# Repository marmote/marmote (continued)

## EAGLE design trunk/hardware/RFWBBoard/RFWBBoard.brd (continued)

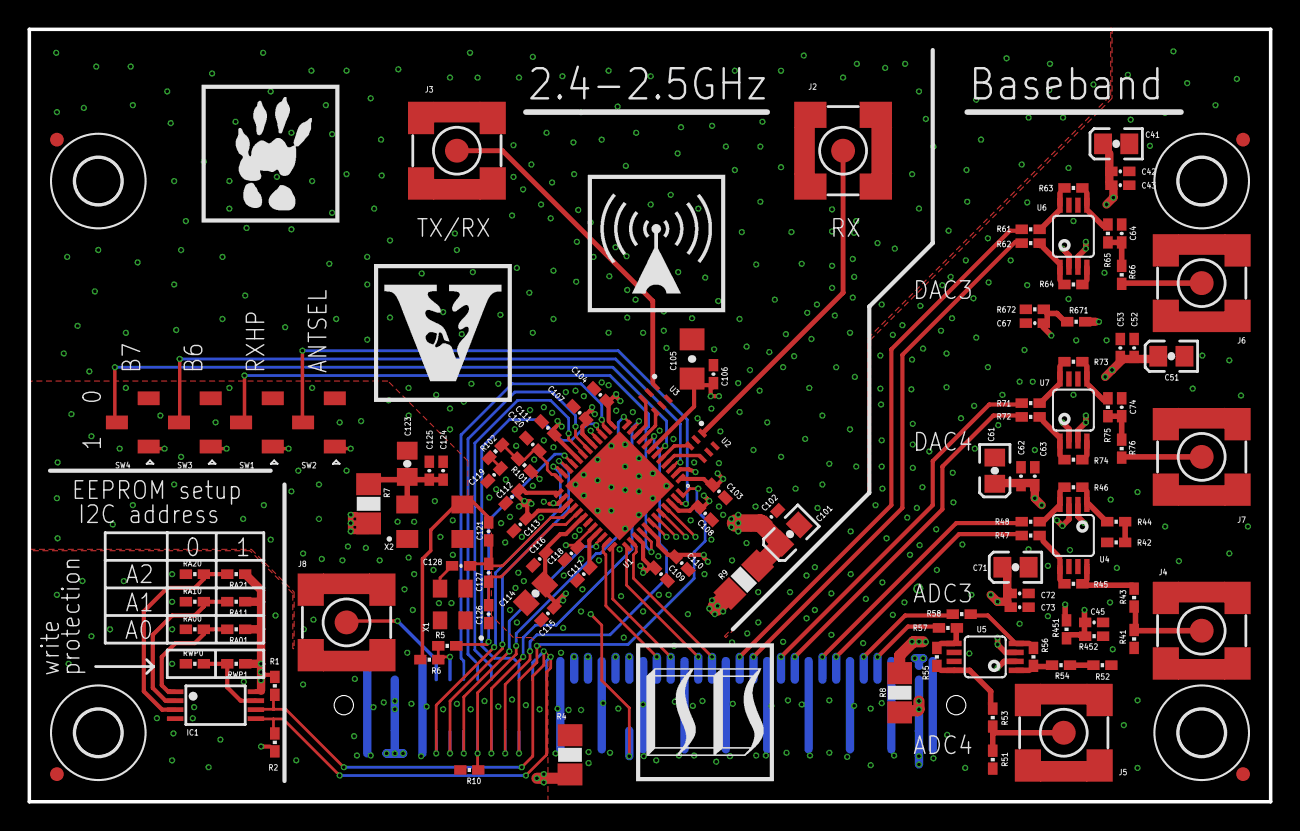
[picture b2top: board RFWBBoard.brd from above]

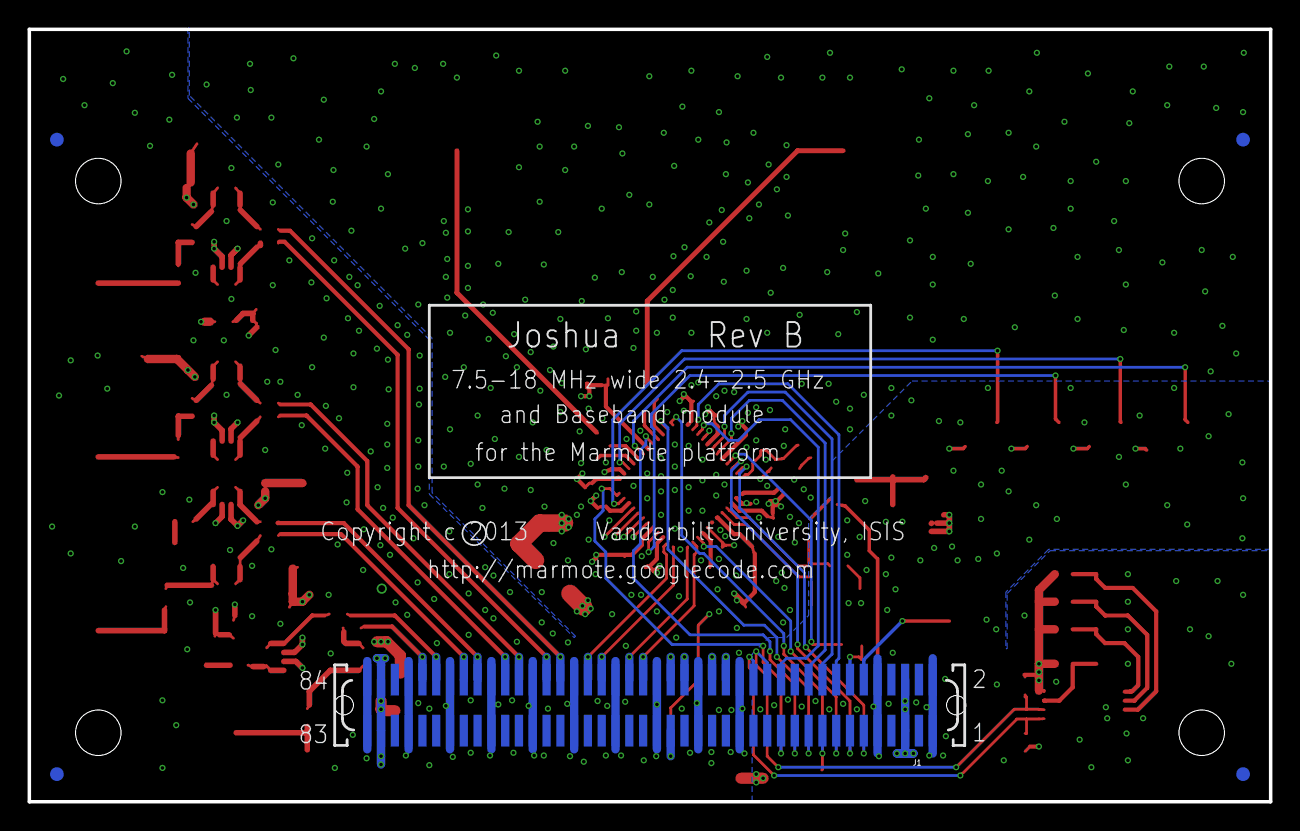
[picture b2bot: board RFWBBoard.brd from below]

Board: 6 copper layers, 90.0 x 56.0 mm, 132 parts (5 on the bottom side), 91 nets.

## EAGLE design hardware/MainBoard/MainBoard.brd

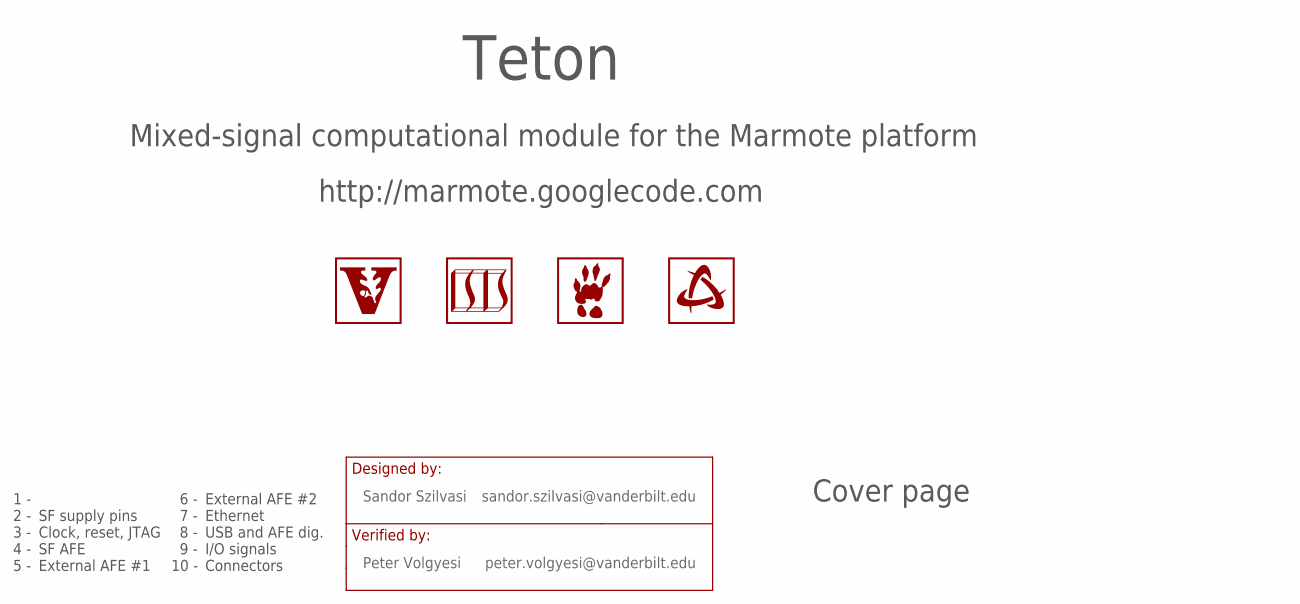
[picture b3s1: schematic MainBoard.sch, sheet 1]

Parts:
LOGO1: LOGO-VANDERBILT-600MIL-10MM-SS; LOGO-VANDERBILT-10MM-SILKSCREEN
LOGO2: LOGO-ISIS-600MIL-10MM-SS; LOGO-ISIS-10MM-SILKSCREEN
LOGO3: LOGO-MARMOTE-600MIL-10MM-SS; LOGO-MARMOTE-10MM-SILKSCREEN
LOGO4: LOGO-SMARTFUSION-600MIL-10MM-SS; LOGO-SMARTFUSION-10MM-SILKSCREEN

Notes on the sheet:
Mixed-signal computational module for the Marmote platform
http://marmote.googlecode.com
1 -
2 -
3 -
4 -
5 -
6 -
7 -
8 -
9 -
10 -

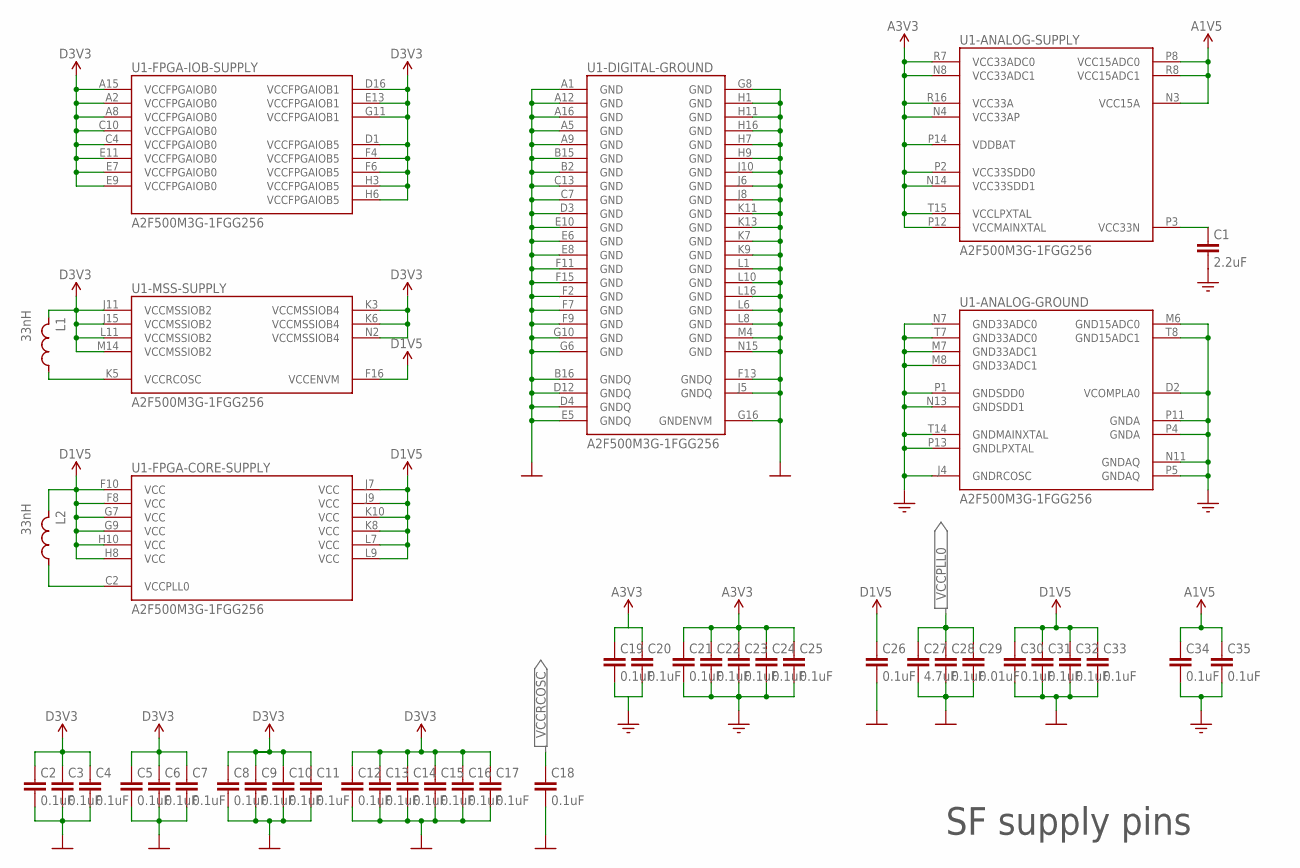
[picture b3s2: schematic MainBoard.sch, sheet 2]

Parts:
C1: 2.2uF; C0402
C2, C3, C4, C5, C6, C7, C8, C9, C10, C11, C12, C13, C14, C15, C16, C17, C18, C19, C20, C21, C22, C23, C24, C25, C26, C28, C30, C31, C32, C33, C34, C35: 0.1uF; C0402
C27: 4.7uF; C0402
C29: 0.01uF; C0402
L1, L2: 33nH; L0603
U1: A2F500M3G-1FGG256; FG256

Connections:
A1V5: C34.1, C35.1, U1.N3 (VCC15A), U1.P8 (VCC15ADC0), U1.R8 (VCC15ADC1); also elsewhere on the board
A3V3: C19.1, C20.1, C21.1, C22.1, C23.1, C24.1, C25.1, U1.N4 (VCC33AP), U1.N8 (VCC33ADC1), U1.N14 (VCC33SDD1), U1.P2 (VCC33SDD0), U1.P12 (VCCMAINXTAL), U1.P14 (VDDBAT), U1.R7 (VCC33ADC0), U1.R16 (VCC33A), U1.T15 (VCCLPXTAL); also elsewhere on the board
AGND: C1.2, C19.2, C20.2, C21.2, C22.2, C23.2, C24.2, C25.2, C34.2, C35.2, U1.D2 (VCOMPLA0), U1.J4 (GNDRCOSC), U1.M6 (GND15ADC0), U1.M7 (GND33ADC1), U1.M8 (GND33ADC1), U1.N7 (GND33ADC0), U1.N11 (GNDAQ), U1.N13 (GNDSDD1), U1.P1 (GNDSDD0), U1.P4 (GNDA), U1.P5 (GNDAQ), U1.P11 (GNDA), U1.P13 (GNDLPXTAL), U1.T7 (GND33ADC0), U1.T8 (GND15ADC1), U1.T14 (GNDMAINXTAL); also elsewhere on the board
D1V5: C26.1, C30.1, C31.1, C32.1, C33.1, L2.2, U1.F8 (VCC), U1.F10 (VCC), U1.F16 (VCCENVM), U1.G7 (VCC), U1.G9 (VCC), U1.H8 (VCC), U1.H10 (VCC), U1.J7 (VCC), U1.J9 (VCC), U1.K8 (VCC), U1.K10 (VCC), U1.L7 (VCC), U1.L9 (VCC); also elsewhere on the board
D3V3: C2.1, C3.1, C4.1, C5.1, C6.1, C7.1, C8.1, C9.1, C10.1, C11.1, C12.1, C13.1, C14.1, C15.1, C16.1, C17.1, L1.2, U1.A2 (VCCFPGAIOB0), U1.A8 (VCCFPGAIOB0), U1.A15 (VCCFPGAIOB0), U1.C4 (VCCFPGAIOB0), U1.C10 (VCCFPGAIOB0), U1.D1 (VCCFPGAIOB5), U1.D16 (VCCFPGAIOB1), U1.E7 (VCCFPGAIOB0), U1.E9 (VCCFPGAIOB0), U1.E11 (VCCFPGAIOB0), U1.E13 (VCCFPGAIOB1), U1.F4 (VCCFPGAIOB5), U1.F6 (VCCFPGAIOB5), U1.G11 (VCCFPGAIOB1), U1.H3 (VCCFPGAIOB5), U1.H6 (VCCFPGAIOB5), U1.J11 (VCCMSSIOB2), U1.J15 (VCCMSSIOB2), U1.K3 (VCCMSSIOB4), U1.K6 (VCCMSSIOB4), U1.L11 (VCCMSSIOB2), U1.M14 (VCCMSSIOB2), U1.N2 (VCCMSSIOB4); also elsewhere on the board
DGND: C2.2, C3.2, C4.2, C5.2, C6.2, C7.2, C8.2, C9.2, C10.2, C11.2, C12.2, C13.2, C14.2, C15.2, C16.2, C17.2, C18.2, C26.2, C27.2, C28.2, C29.2, C30.2, C31.2, C32.2, C33.2, U1.A1 (GND), U1.A5 (GND), U1.A9 (GND), U1.A12 (GND), U1.A16 (GND), U1.B2 (GND), U1.B15 (GND), U1.B16 (GNDQ), U1.C7 (GND), U1.C13 (GND), U1.D3 (GND), U1.D4 (GNDQ), U1.D12 (GNDQ), U1.E5 (GNDQ), U1.E6 (GND), U1.E8 (GND), U1.E10 (GND), U1.F2 (GND), U1.F7 (GND), U1.F9 (GND), U1.F11 (GND), U1.F13 (GNDQ), U1.F15 (GND), U1.G6 (GND), U1.G8 (GND), U1.G10 (GND), U1.G16 (GNDENVM), U1.H1 (GND), U1.H7 (GND), U1.H9 (GND), U1.H11 (GND), U1.H16 (GND), U1.J5 (GNDQ), U1.J6 (GND), U1.J8 (GND), U1.J10 (GND), U1.K7 (GND), U1.K9 (GND), U1.K11 (GND), U1.K13 (GND), U1.L1 (GND), U1.L6 (GND), U1.L8 (GND), U1.L10 (GND), U1.L16 (GND), U1.M4 (GND), U1.N15 (GND); also elsewhere on the board
VCC3N: C1.1, U1.P3 (VCC33N)
VCCPLL0: C27.1, C28.1, C29.1, L2.1, U1.C2 (VCCPLL0)
VCCRCOSC: C18.1, L1.1, U1.K5 (VCCRCOSC)

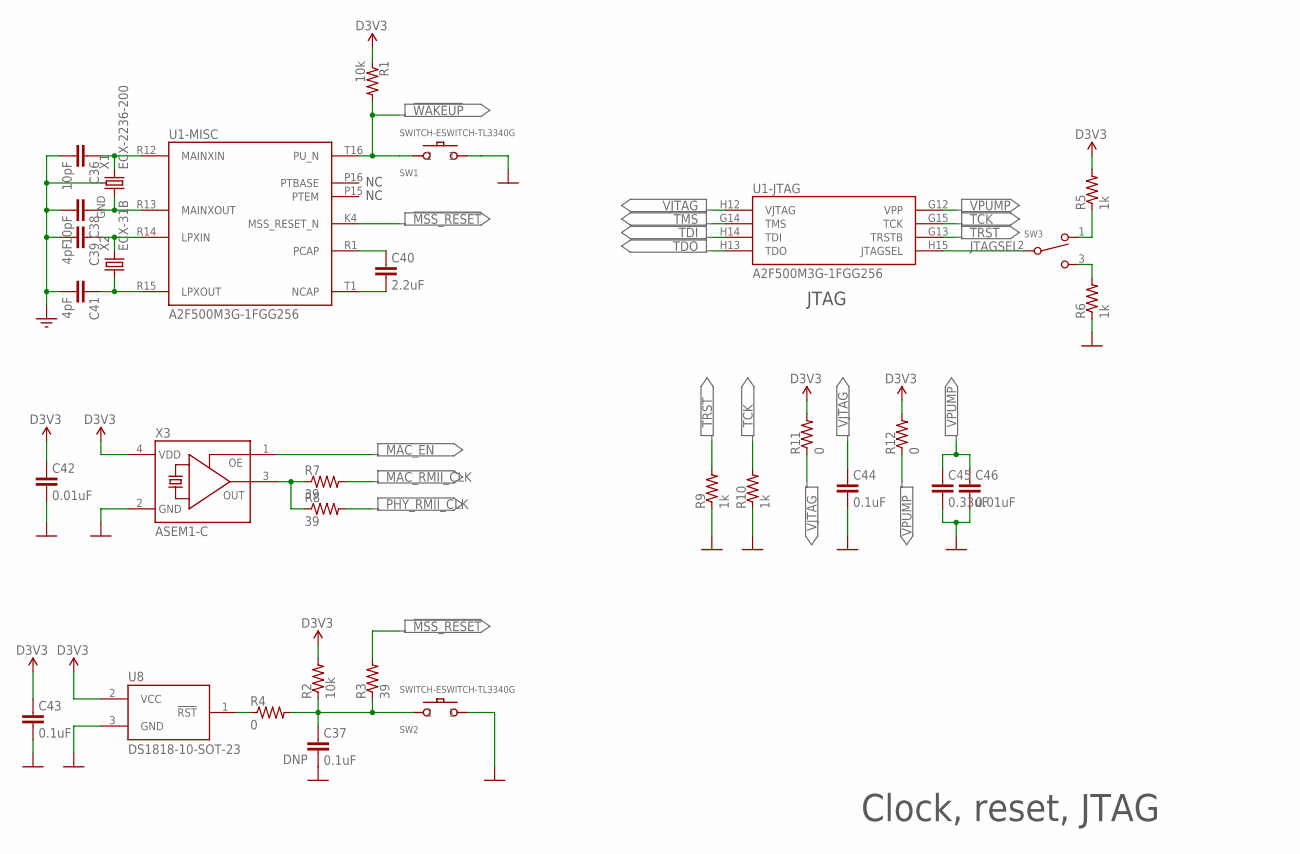
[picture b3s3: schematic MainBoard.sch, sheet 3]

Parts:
C36, C38: 10pF; C0402
C37, C43, C44: 0.1uF; C0402
C39, C41: 4pF; C0402
C40: 2.2uF; C0402
C42: 0.01uF; C0402
C45: 0.33uF; C0402
C46: 0.01uF; C0402; VOLTAGE-RATING 16V
R1, R2: 10k; R0402
R3, R7, R8: 39; R0402
R4, R11, R12: 0; R0402
R5, R6, R9, R10: 1k; R0402
SW1, SW2: SWITCH-ESWITCH-TL3340G; TL3340
SW3: SWITCH-CJS-1200TA; SWITCH-DIP-CJS
U1: A2F500M3G-1FGG256; FG256
U8: DS1818-10-SOT-23; SOT23-3L
X1: ECX-2236-200; ECX-2236; DIGI-KEY# XC1556CT-ND
X2: ECX-31B
X3: ASEM1-C; ASEM1; MPN ASEM1-50.000MHZ-LC-T

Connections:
!MSS_RESET: R3.2, U1.K4 (MSS_RESET_N); also elsewhere on the board
!MSS_RESET_PB: C37.1, R2.1, R3.1, R4.2, SW2.2
!WAKEUP: R1.2, SW1.2, U1.T16 (PU_N); also elsewhere on the board
AGND: C36.2, C38.2, C39.2, C41.2, X1.2 (GND), X1.4 (GND); also elsewhere on the board
D3V3: C42.1, C43.1, R1.1, R2.2, R5.2, R11.2, R12.2, U8.2 (VCC), X3.4 (VDD); also elsewhere on the board
DGND: C37.2, C42.2, C43.2, C44.2, C45.2, C46.2, R6.1, R9.1, R10.1, SW1.1, SW1.3 (1), SW2.1, SW2.3 (1), U8.3 (GND), X3.2 (GND); also elsewhere on the board
EXTIC-RST: R4.1, U8.1 (!RST)
FPGATAP: R5.1, SW3.1
JTAGSEL: SW3.2, U1.H15 (JTAGSEL)
LPXIN: C39.1, U1.R14 (LPXIN), X2.2
LPXOUT: C41.1, U1.R15 (LPXOUT), X2.1
MAC_EN: X3.1 (OE); also elsewhere on the board
MAC_RMII_CLK: R7.2; also elsewhere on the board
MAINXIN: C36.1, U1.R12 (MAINXIN), X1.3 (2)
MAINXOUT: C38.1, U1.R13 (MAINXOUT), X1.1
MSSTAP: R6.2, SW3.3
NCAP: C40.2, U1.T1 (NCAP)
PCAP: C40.1, U1.R1 (PCAP)
PHY_RMII_CLK: R8.2; also elsewhere on the board
RMII_CLK: R7.1, R8.1, X3.3 (FO)
TCK: R10.2, U1.G15 (TCK); also elsewhere on the board
TDI: U1.H14 (TDI); also elsewhere on the board
TDO: U1.H13 (TDO); also elsewhere on the board
TMS: U1.G14 (TMS); also elsewhere on the board
TRST: R9.2, U1.G13 (TRSTB); also elsewhere on the board
VJTAG: C44.1, R11.1, U1.H12 (VJTAG); also elsewhere on the board
VPUMP: C45.1, C46.1, R12.1, U1.G12 (VPP); also elsewhere on the board

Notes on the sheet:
JTAG

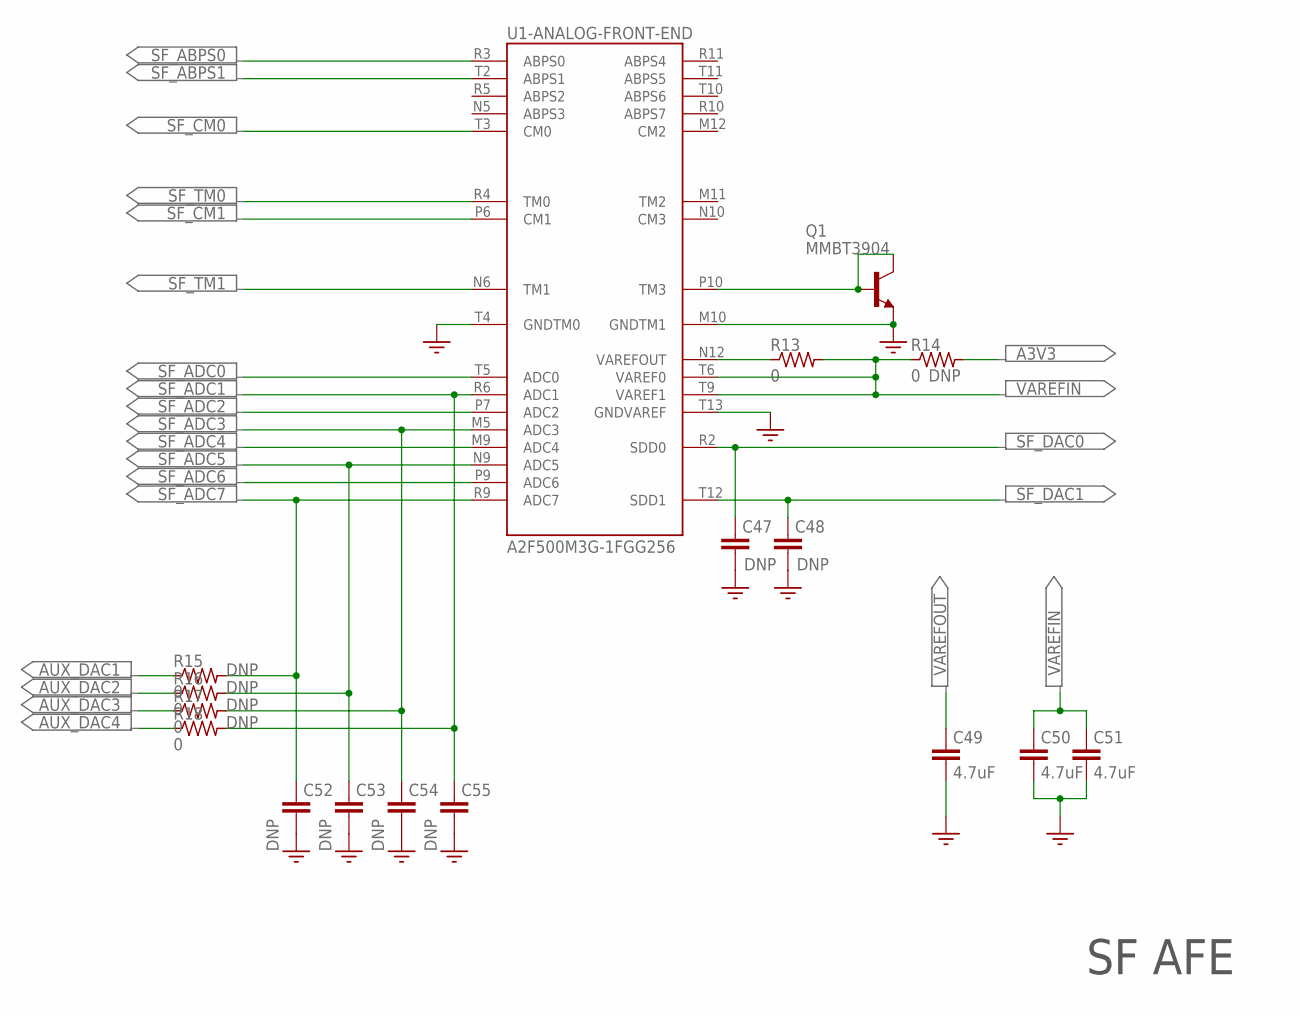
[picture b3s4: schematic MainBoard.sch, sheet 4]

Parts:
C47, C48, C52, C53, C54, C55: C0402
C49, C50, C51: 4.7uF; C0402
Q1: MMBT3904; SOT23-3L
R13, R14, R15, R16, R17, R18: 0; R0402
U1: A2F500M3G-1FGG256; FG256

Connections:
A3V3: R14.2; also elsewhere on the board
AGND: C47.2, C48.2, C49.2, C50.2, C51.2, C52.2, C53.2, C54.2, C55.2, Q1.2 (E), U1.M10 (GNDTM1), U1.T4 (GNDTM0), U1.T13 (GNDVAREF); also elsewhere on the board
AUX_DAC1: R15.1; also elsewhere on the board
AUX_DAC2: R16.1; also elsewhere on the board
AUX_DAC3: R17.1; also elsewhere on the board
AUX_DAC4: R18.1; also elsewhere on the board
SF_ABPS0: U1.R3 (ABPS0); also elsewhere on the board
SF_ABPS1: U1.T2 (ABPS1); also elsewhere on the board
SF_ADC0: U1.T5 (ADC0); also elsewhere on the board
SF_ADC1: C55.1, R18.2, U1.R6 (ADC1); also elsewhere on the board
SF_ADC2: U1.P7 (ADC2); also elsewhere on the board
SF_ADC3: C54.1, R17.2, U1.M5 (ADC3); also elsewhere on the board
SF_ADC4: U1.M9 (ADC4); also elsewhere on the board
SF_ADC5: C53.1, R16.2, U1.N9 (ADC5); also elsewhere on the board
SF_ADC6: U1.P9 (ADC6); also elsewhere on the board
SF_ADC7: C52.1, R15.2, U1.R9 (ADC7); also elsewhere on the board
SF_CM0: U1.T3 (CM0); also elsewhere on the board
SF_CM1: U1.P6 (CM1); also elsewhere on the board
SF_DAC0: C47.1, U1.R2 (SDD0); also elsewhere on the board
SF_DAC1: C48.1, U1.T12 (SDD1); also elsewhere on the board
SF_TM0: U1.R4 (TM0); also elsewhere on the board
SF_TM1: U1.N6 (TM1); also elsewhere on the board
SF_TM3: Q1.1 (B), Q1.3 (C), U1.P10 (TM3)
VAREFIN: C50.1, C51.1, R13.2, R14.1, U1.T6 (VAREF0), U1.T9 (VAREF1)
VAREFOUT: C49.1, R13.1, U1.N12 (VAREFOUT)

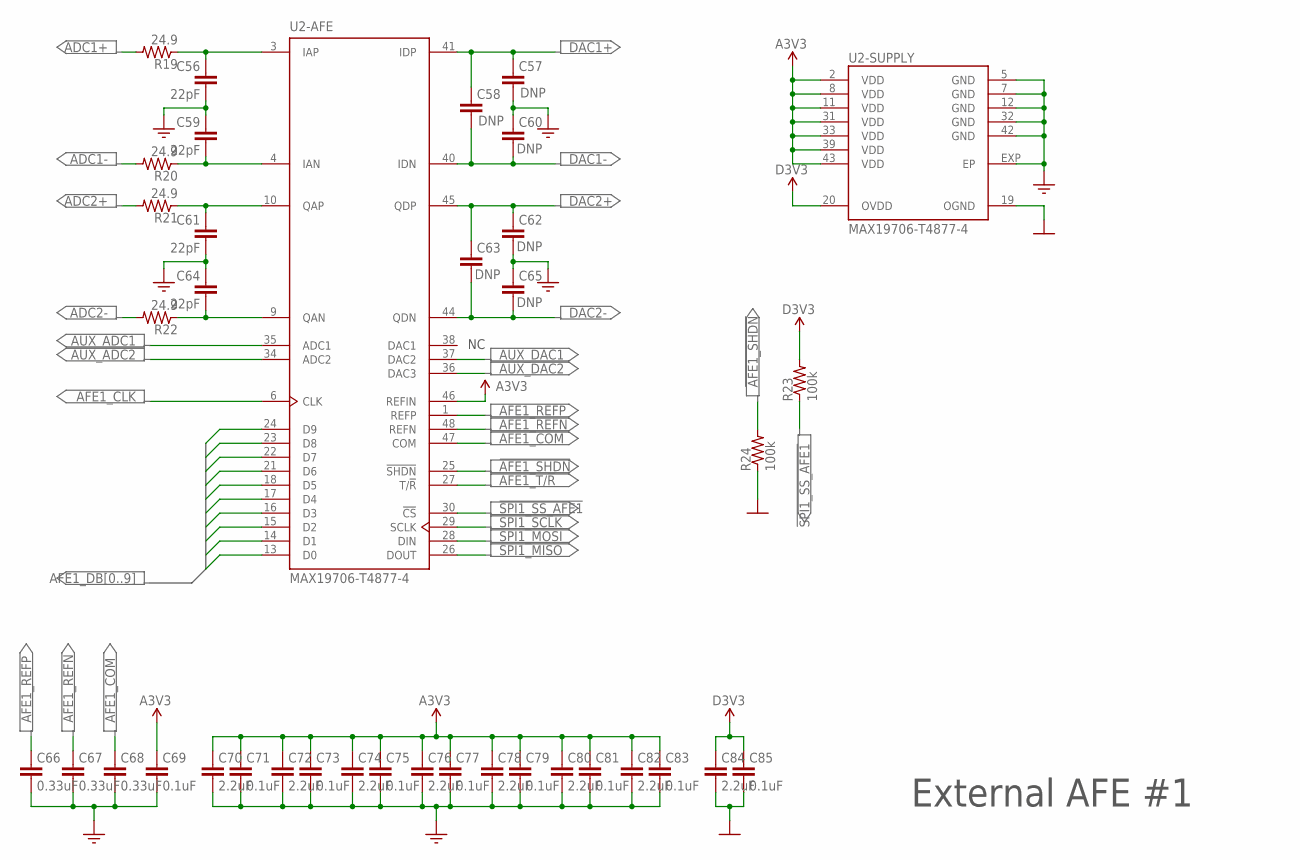
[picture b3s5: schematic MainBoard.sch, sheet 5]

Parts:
C56, C59, C61, C64: 22pF; C0402
C57, C58, C60, C62, C63, C65: C0402
C66, C67, C68: 0.33uF; C0402
C69, C71, C73, C75, C77, C79, C81, C83, C85: 0.1uF; C0402
C70, C72, C74, C76, C78, C80, C82, C84: 2.2uF; C0402
R19, R20, R21, R22: 24.9; R0402
R23, R24: 100k; R0402
U2: MAX19706-T4877-4; TQFN-48

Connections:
!AFE1_SHDN: R24.2, U2.25 (!SHDN); also elsewhere on the board
!SPI1_SS_AFE1: R23.1, U2.30 (!CS); also elsewhere on the board
A3V3: C69.1, C70.1, C71.1, C72.1, C73.1, C74.1, C75.1, C76.1, C77.1, C78.1, C79.1, C80.1, C81.1, C82.1, C83.1, U2.2 (VDD), U2.8 (VDD), U2.11 (VDD), U2.31 (VDD), U2.33 (VDD), U2.39 (VDD), U2.43 (VDD), U2.46 (REFIN); also elsewhere on the board
ADC1+: R19.2; also elsewhere on the board
ADC1-: R20.2; also elsewhere on the board
ADC1-IAN: C59.2, R20.1, U2.4 (IAN)
ADC1-IAP: C56.1, R19.1, U2.3 (IAP)
ADC2+: R21.2; also elsewhere on the board
ADC2-: R22.2; also elsewhere on the board
ADC2-QAN: C64.2, R22.1, U2.9 (QAN)
ADC2-QAP: C61.1, R21.1, U2.10 (QAP)
AFE1_CLK: U2.6 (CLK); also elsewhere on the board
AFE1_COM: C68.1, U2.47 (COM)
AFE1_DB0: U2.13 (D0); also elsewhere on the board
AFE1_DB1: U2.14 (D1); also elsewhere on the board
AFE1_DB2: U2.15 (D2); also elsewhere on the board
AFE1_DB3: U2.16 (D3); also elsewhere on the board
AFE1_DB4: U2.17 (D4); also elsewhere on the board
AFE1_DB5: U2.18 (D5); also elsewhere on the board
AFE1_DB6: U2.21 (D6); also elsewhere on the board
AFE1_DB7: U2.22 (D7); also elsewhere on the board
AFE1_DB8: U2.23 (D8); also elsewhere on the board
AFE1_DB9: U2.24 (D9); also elsewhere on the board
AFE1_REFN: C67.1, U2.48 (REFN)
AFE1_REFP: C66.1, U2.1 (REFP)
AFE1_T/!R: U2.27 (T/!R); also elsewhere on the board
AGND: C56.2, C57.2, C59.1, C60.1, C61.2, C62.2, C64.1, C65.1, C66.2, C67.2, C68.2, C69.2, C70.2, C71.2, C72.2, C73.2, C74.2, C75.2, C76.2, C77.2, C78.2, C79.2, C80.2, C81.2, C82.2, C83.2, U2.5 (GND), U2.7 (GND), U2.12 (GND), U2.32 (GND), U2.42 (GND), U2.EXP (EP); also elsewhere on the board
AUX_ADC1: U2.35 (ADC1)
AUX_ADC2: U2.34 (ADC2)
AUX_DAC1: U2.37 (DAC2); also elsewhere on the board
AUX_DAC2: U2.36 (DAC3); also elsewhere on the board
D3V3: C84.1, C85.1, R23.2, U2.20 (OVDD); also elsewhere on the board
DAC1+: C57.1, C58.1, U2.41 (IDP); also elsewhere on the board
DAC1-: C58.2, C60.2, U2.40 (IDN); also elsewhere on the board
DAC2+: C62.1, C63.1, U2.45 (QDP); also elsewhere on the board
DAC2-: C63.2, C65.2, U2.44 (QDN); also elsewhere on the board
DGND: C84.2, C85.2, R24.1, U2.19 (OGND); also elsewhere on the board
SPI1_MISO: U2.26 (DOUT); also elsewhere on the board
SPI1_MOSI: U2.28 (DIN); also elsewhere on the board
SPI1_SCLK: U2.29 (SCLK); also elsewhere on the board

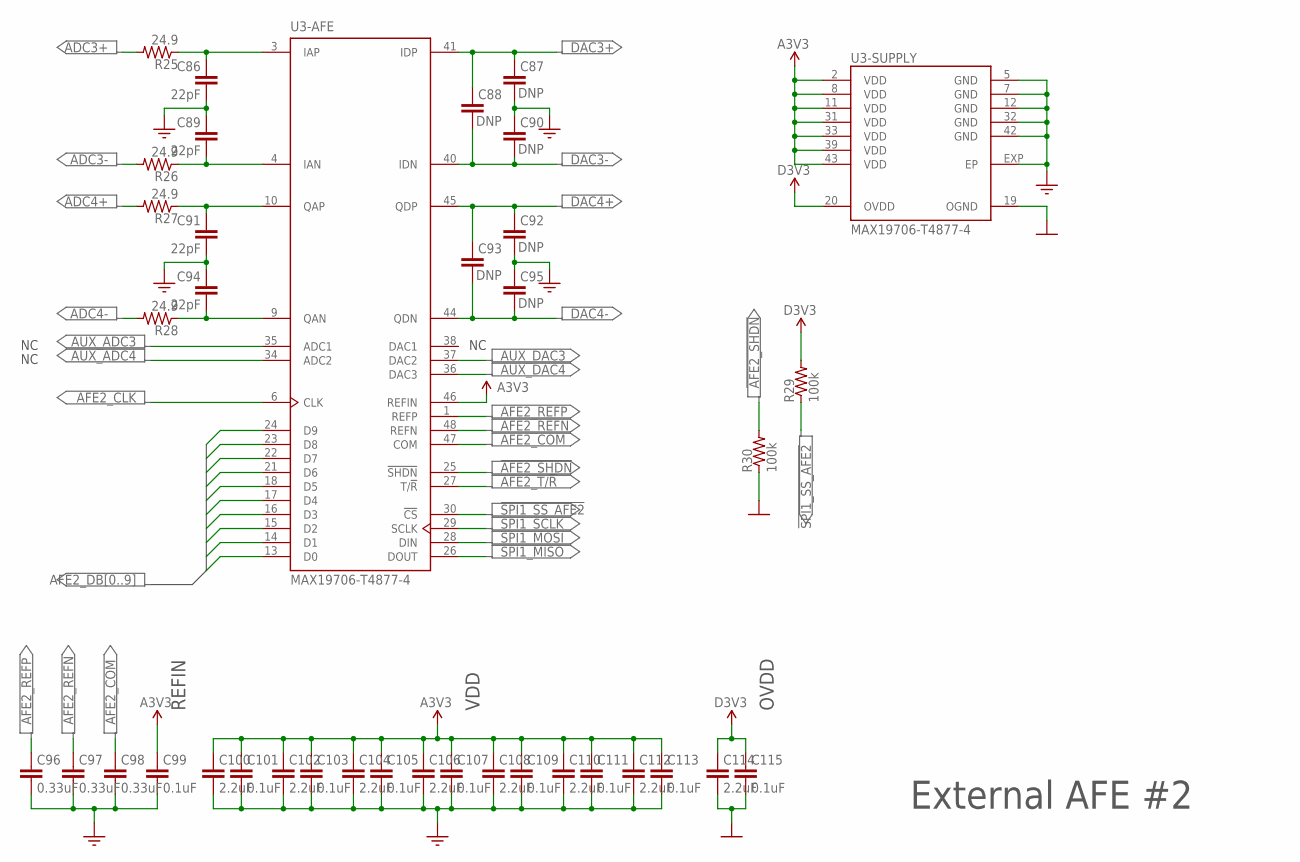
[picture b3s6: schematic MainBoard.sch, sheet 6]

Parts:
C86, C89, C91, C94: 22pF; C0402
C87, C88, C90, C92, C93, C95: C0402
C96, C97, C98: 0.33uF; C0402
C99, C101, C103, C105, C107, C109, C111, C113, C115: 0.1uF; C0402
C100, C102, C104, C106, C108, C110, C112, C114: 2.2uF; C0402
R25, R26, R27, R28: 24.9; R0402
R29, R30: 100k; R0402
U3: MAX19706-T4877-4; TQFN-48

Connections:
!AFE2_SHDN: R30.2, U3.25 (!SHDN); also elsewhere on the board
!SPI1_SS_AFE2: R29.1, U3.30 (!CS); also elsewhere on the board
A3V3: C99.1, C100.1, C101.1, C102.1, C103.1, C104.1, C105.1, C106.1, C107.1, C108.1, C109.1, C110.1, C111.1, C112.1, C113.1, U3.2 (VDD), U3.8 (VDD), U3.11 (VDD), U3.31 (VDD), U3.33 (VDD), U3.39 (VDD), U3.43 (VDD), U3.46 (REFIN); also elsewhere on the board
ADC3+: R25.2; also elsewhere on the board
ADC3-: R26.2; also elsewhere on the board
ADC3-IAN: C89.2, R26.1, U3.4 (IAN)
ADC3-IAP: C86.1, R25.1, U3.3 (IAP)
ADC4+: R27.2; also elsewhere on the board
ADC4-: R28.2; also elsewhere on the board
ADC4-QAN: C94.2, R28.1, U3.9 (QAN)
ADC4-QAP: C91.1, R27.1, U3.10 (QAP)
AFE2_CLK: U3.6 (CLK); also elsewhere on the board
AFE2_COM: C98.1, U3.47 (COM)
AFE2_DB0: U3.13 (D0); also elsewhere on the board
AFE2_DB1: U3.14 (D1); also elsewhere on the board
AFE2_DB2: U3.15 (D2); also elsewhere on the board
AFE2_DB3: U3.16 (D3); also elsewhere on the board
AFE2_DB4: U3.17 (D4); also elsewhere on the board
AFE2_DB5: U3.18 (D5); also elsewhere on the board
AFE2_DB6: U3.21 (D6); also elsewhere on the board
AFE2_DB7: U3.22 (D7); also elsewhere on the board
AFE2_DB8: U3.23 (D8); also elsewhere on the board
AFE2_DB9: U3.24 (D9); also elsewhere on the board
AFE2_REFN: C97.1, U3.48 (REFN)
AFE2_REFP: C96.1, U3.1 (REFP)
AFE2_T/!R: U3.27 (T/!R); also elsewhere on the board
AGND: C86.2, C87.2, C89.1, C90.1, C91.2, C92.2, C94.1, C95.1, C96.2, C97.2, C98.2, C99.2, C100.2, C101.2, C102.2, C103.2, C104.2, C105.2, C106.2, C107.2, C108.2, C109.2, C110.2, C111.2, C112.2, C113.2, U3.5 (GND), U3.7 (GND), U3.12 (GND), U3.32 (GND), U3.42 (GND), U3.EXP (EP); also elsewhere on the board
AUX_ADC3: U3.35 (ADC1)
AUX_ADC4: U3.34 (ADC2)
AUX_DAC3: U3.37 (DAC2); also elsewhere on the board
AUX_DAC4: U3.36 (DAC3); also elsewhere on the board
D3V3: C114.1, C115.1, R29.2, U3.20 (OVDD); also elsewhere on the board
DAC3+: C87.1, C88.1, U3.41 (IDP); also elsewhere on the board
DAC3-: C88.2, C90.2, U3.40 (IDN); also elsewhere on the board
DAC4+: C92.1, C93.1, U3.45 (QDP); also elsewhere on the board
DAC4-: C93.2, C95.2, U3.44 (QDN); also elsewhere on the board
DGND: C114.2, C115.2, R30.1, U3.19 (OGND); also elsewhere on the board
SPI1_MISO: U3.26 (DOUT); also elsewhere on the board
SPI1_MOSI: U3.28 (DIN); also elsewhere on the board
SPI1_SCLK: U3.29 (SCLK); also elsewhere on the board

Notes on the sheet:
VDD
OVDD
REFIN

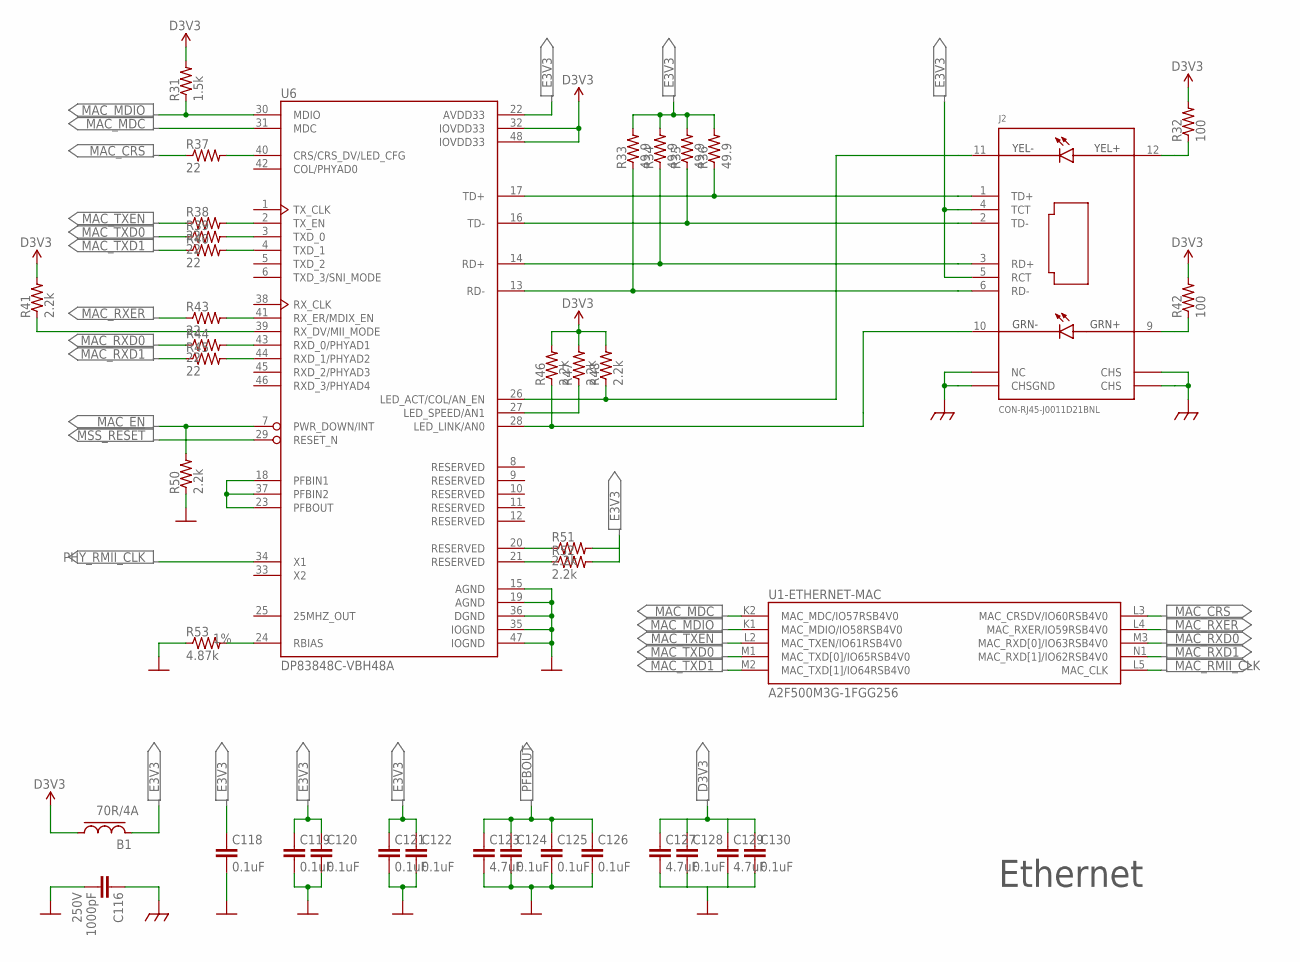
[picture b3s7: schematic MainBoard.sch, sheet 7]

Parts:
B1: 70R/4A; L0603
C116: 1000pF; C0805; RATING 250V
C118, C119, C120, C121, C122, C124, C125, C126, C128, C130: 0.1uF; C0402
C123, C127, C129: 4.7uF; C0402
J2: CON-RJ45-J0011D21BNL; J0011D21B
R31: 1.5k; R0402
R32, R42: 100; R0402
R33, R34, R35, R36: 49.9; R0402
R37, R38, R39, R40, R43, R44, R45: 22; R0402
R41, R46, R47, R48, R50, R51, R52: 2.2k; R0402
R53: 4.87k; R0402; TOLERANCE 1%
U1: A2F500M3G-1FGG256; FG256
U6: DP83848C-VBH48A; LQFP-48

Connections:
!MSS_RESET: U6.29 (RESET_N); also elsewhere on the board
COM+: J2.9 (GRN+), R42.1
CRS: R37.2, U6.40 (CRS/CRS_DV/LED_CFG)
D3V3: B1.1, C127.1, C128.1, C129.1, C130.1, R31.2, R32.2, R41.2, R42.2, R46.2, R47.2, R48.2, U6.32 (IOVDD33), U6.48 (IOVDD33); also elsewhere on the board
DGND: C116.2, C118.2, C119.2, C120.2, C121.2, C122.2, C123.2, C124.2, C125.2, C126.2, C127.2, C128.2, C129.2, C130.2, R50.1, R53.1, U6.15 (AGND), U6.19 (AGND), U6.35 (IOGND), U6.36 (DGND), U6.47 (IOGND); also elsewhere on the board
E3V3: B1.2, C118.1, C119.1, C120.1, C121.1, C122.1, J2.4 (TCT), J2.5 (RCT), R33.2, R34.2, R35.2, R36.2, R51.2, R52.2, U6.22 (AVDD33)
EGND: C116.1, J2.7 (NC), J2.8 (CHSGND), J2.H$1 (CHS), J2.H$2 (CHS)
ETH-RBIAS: R53.2, U6.24 (RBIAS)
LED_ETH_ACT: J2.11 (YEL-), R48.1, U6.26 (LED_ACT/COL/AN_EN)
LED_ETH_LINK: J2.10 (GRN-), R46.1, U6.28 (LED_LINK/AN0)
LED_PHY_SPEED: R47.1, U6.27 (LED_SPEED/AN1)
MAC_CRS: R37.1, U1.L3 (MAC_CRSDV/IO60RSB4V0)
MAC_EN: R50.2, U6.7 (PWR_DOWN/INT); also elsewhere on the board
MAC_MDC: U1.K2 (MAC_MDC/IO57RSB4V0), U6.31 (MDC)
MAC_MDIO: R31.1, U1.K1 (MAC_MDIO/IO58RSB4V0), U6.30 (MDIO)
MAC_RMII_CLK: U1.L5 (MAC_CLK); also elsewhere on the board
MAC_RXD0: R44.1, U1.M3 (MAC_RXD[0]/IO63RSB4V0)
MAC_RXD1: R45.1, U1.N1 (MAC_RXD[1]/IO62RSB4V0)
MAC_RXER: R43.1, U1.L4 (MAC_RXER/IO59RSB4V0)
MAC_TXD0: R39.1, U1.M1 (MAC_TXD[0]/IO65RSB4V0)
MAC_TXD1: R40.1, U1.M2 (MAC_TXD[1]/IO64RSB4V0)
MAC_TXEN: R38.1, U1.L2 (MAC_TXEN/IO61RSB4V0)
PFBOUT: C123.1, C124.1, C125.1, C126.1, U6.18 (PFBIN1), U6.23 (PFBOUT), U6.37 (PFBIN2)
PHY_RMII_CLK: U6.34 (X1); also elsewhere on the board
RD+: J2.3 (RD+), R34.1, U6.14 (RD+)
RD-: J2.6 (RD-), R33.1, U6.13 (RD-)
RSVD-P20: R51.1, U6.20 (RESERVED)
RSVD-P21: R52.1, U6.21 (RESERVED)
RXD_0/PHYAD1: R44.2, U6.43 (RXD_0/PHYAD1)
RXD_1/PHYAD2: R45.2, U6.44 (RXD_1/PHYAD2)
RX_DV: R41.1, U6.39 (RX_DV/MII_MODE)
RX_ER: R43.2, U6.41 (RX_ER/MDIX_EN)
TD+: J2.1 (TD+), R36.1, U6.17 (TD+)
TD-: J2.2 (TD-), R35.1, U6.16 (TD-)
TXD_0: R39.2, U6.3 (TXD_0)
TXD_1: R40.2, U6.4 (TXD_1)
TX_EN: R38.2, U6.2 (TX_EN)
YEL+: J2.12 (YEL+), R32.1
